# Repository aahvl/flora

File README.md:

### FloraPad

Here is a quick look at a sleek little macro pad I’ve been working on. It’s super compact but packs a ton of utility into a really small macropad.
The setup includes:
2 Cherry MX switches (and yes you can swap out the keycaps whenever you want).
A rotary encoder (the volume knob is also fully customizable with your own knob).
A custom engraved logo on the case, finished off with nice, smooth filleted corners.
-
The Struggles:
The biggest headache with this build was definitely getting the faceplate right. Trying to perfectly trace and align the cutouts for the switches and the rotary encoder so everything lined up cleanly, took a ridiculous amount of trial and error.
-
## Photos

## BOM

| Component | Approx. Price |
|----------|----------|
| 2x Cherry MX Switches  | £5   |
| 2x KeyCaps  | £3   |
| 1x EC11E Rotary Encoder  | £6   |
| 1x SEEED Studio XIAO RP2040  | £20   |
| 1x PCB  | £3   |
| 1x 3D Printing  | ???   |

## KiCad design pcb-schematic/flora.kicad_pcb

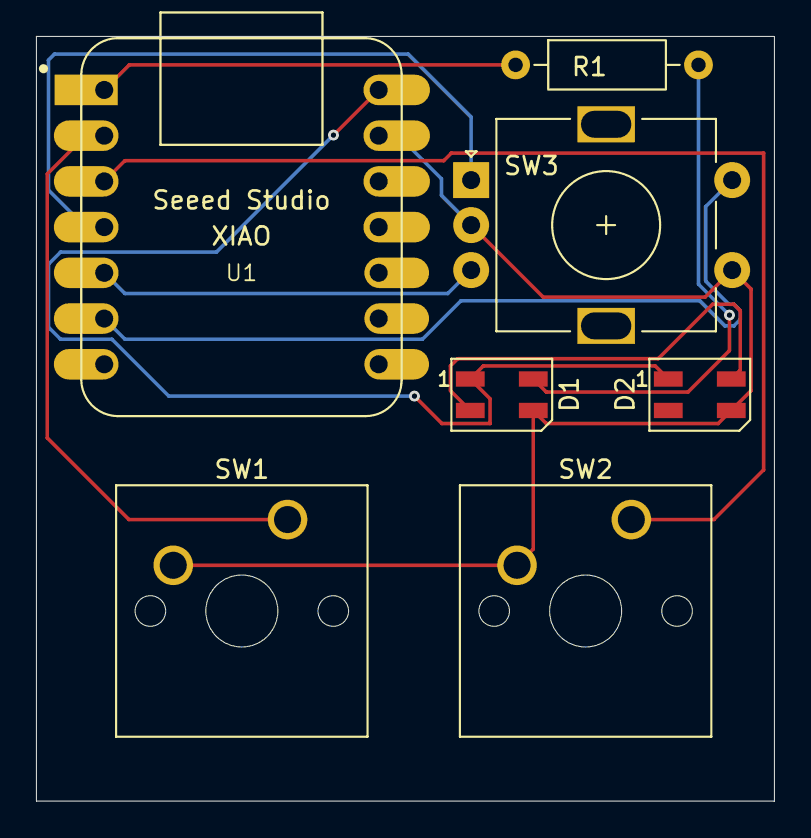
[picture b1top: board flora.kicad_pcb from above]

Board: 2 copper layers, 41.0 x 42.5 mm, 7 parts (0 on the bottom side), 10 nets.

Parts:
D1: LED1; LED_SK6812MINI_PLCC4_3.5x3.5mm_P1.75mm
D2: LED2; LED_SK6812MINI_PLCC4_3.5x3.5mm_P1.75mm
R1: 330; R_Axial_DIN0207_L6.3mm_D2.5mm_P10.16mm_Horizontal
SW1, SW2: SW_Push; SW_Cherry_MX_1.00u_PCB
SW3: RE_SW_MP; RotaryEncoder_Alps_EC11E-Switch_Vertical_H20mm
U1: MOUDLE-SEEEDUINO-XIAO; XIAO-Generic-Hybrid-14P-2.54-21X17.8MM

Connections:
+5V: D1.1 (VDD), D2.1 (VDD), U1.14 (5V)
GND: D1.3 (VSS), D2.3 (VSS), SW1.2, SW2.2, SW3.C, SW3.S1, U1.13 (GND)
GPIO_D0: R1.1, U1.1 (PA02_A0_D0)
GPIO_D1: SW1.1, U1.2 (PA4_A1_D1)
GPIO_D2: SW2.1, U1.3 (PA10_A2_D2)
GPIO_D3: SW3.A, U1.4 (PA11_A3_D3)
GPIO_D4: SW3.B, U1.5 (PA8_A4_D4_SDA)
GPIO_D5: SW3.S2, U1.6 (PA9_A5_D5_SCL)
unnamed: D1.4 (DIN), R1.2
unnamed: D1.2 (DOUT), D2.4 (DIN)

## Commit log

2026-06-01 KICAD SCHEMATIC + PCB DONE!!!
2026-06-01 Add initial journal entries for Flora project
2026-06-04 Add README.md with project details and BOM
2026-06-04 Document CAD design process in JOURNAL.md
    Added a section about CAD design process and custom plate creation.
2026-06-04 finally done!
2026-06-04 Update BOM section with table format and prices
2026-06-04 firmware addition!
2026-06-22 Enhance README with detailed macropad description
    Updated description to include details about Cherry MX switches and rotary encoder.
2026-06-22 Enhance README with detailed FloraPad description
    Expanded the description of the FloraPad macro pad, detailing its features and the challenges faced during its build.
